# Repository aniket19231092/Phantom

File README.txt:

Phantom ESP32
A lightweight open-source bicycle navigation computer built with the ESP32.

Phantom is a DIY GPS cycling computer designed for outdoor use. It combines an ESP32, u-blox MAX-M10M GPS receiver, Sharp Memory LCD, and microSD card to create a low-power navigation device capable of displaying maps, tracking rides, and providing real-time cycling metrics. Checkout the Pictures folder for pictures of the PCB and enclosure.

The Sharp Memory LCD provides excellent sunlight readability while consuming very little power, making it ideal for long rides.

This is a good project for those getting into embedded electronics and SMD soldering.
---
CAD
Only two parts are needed to be 3D printed, the top and bottom enclosure, which are found in the CAD folder. ABS is preferred because it needs to be able to
withstand the Sun. For assembly 4 M3 screws are needed, about 4-6mm in length is needed.

---
Features

- 🗺️ Offline map rendering from microSD card
- 📍 Real-time GPS positioning using the u-blox MAX-M10M
- 🚴 Live cycling data
  - Current speed
  - Average speed
  - Trip distance
  - Total distance
  - Heading
  - Ride time
- 🧭 Turn-by-turn capable map interface (planned)
- 💾 GPX ride logging to SD card
- 🌞 Sunlight-readable Sharp Memory LCD
- 🔋 Low power design for extended battery life
- 📡 Fast satellite acquisition with multi-band GNSS support
- Bluetooth capabilities for uploading to fitness apps such as Strava

---
Hardware

| Component | Description |
|------------|-------------|
| ESP32 | Main processor |
| MAX-M10M GPS | High-performance GNSS receiver |
| Sharp Memory LCD | Outdoor-readable display |
| microSD Card Module | Offline maps and GPX storage |
| Li-Ion/LiPo Battery | Portable power |
| Battery Charger | USB charging circuit|
| Handlebar Mount | Bicycle mounting system |

Offline Maps

Maps are stored on the microSD card and loaded as needed.

Possible formats include:

- Raster map tiles
- Vector tiles (future)
- Custom compressed tile database

The map renderer centers on the current GPS position while displaying nearby roads and paths.

---

Ride Data

The computer continuously records:

- Current speed
- Average speed
- Maximum speed
- Total distance
- Ride duration
- GPS track
- Timestamp
- Latitude
- Longitude

Tracks are stored as GPX files for later upload to services such as Strava or Garmin Connect.

---

Why Sharp Memory LCD?

Unlike TFT or OLED displays, the Sharp Memory LCD offers:

- Excellent readability in direct sunlight
- Extremely low power consumption
- No backlight required during daytime
- Fast refresh for navigation
- Long battery life

These characteristics make it particularly well-suited for bicycle computers and outdoor GPS devices.

---

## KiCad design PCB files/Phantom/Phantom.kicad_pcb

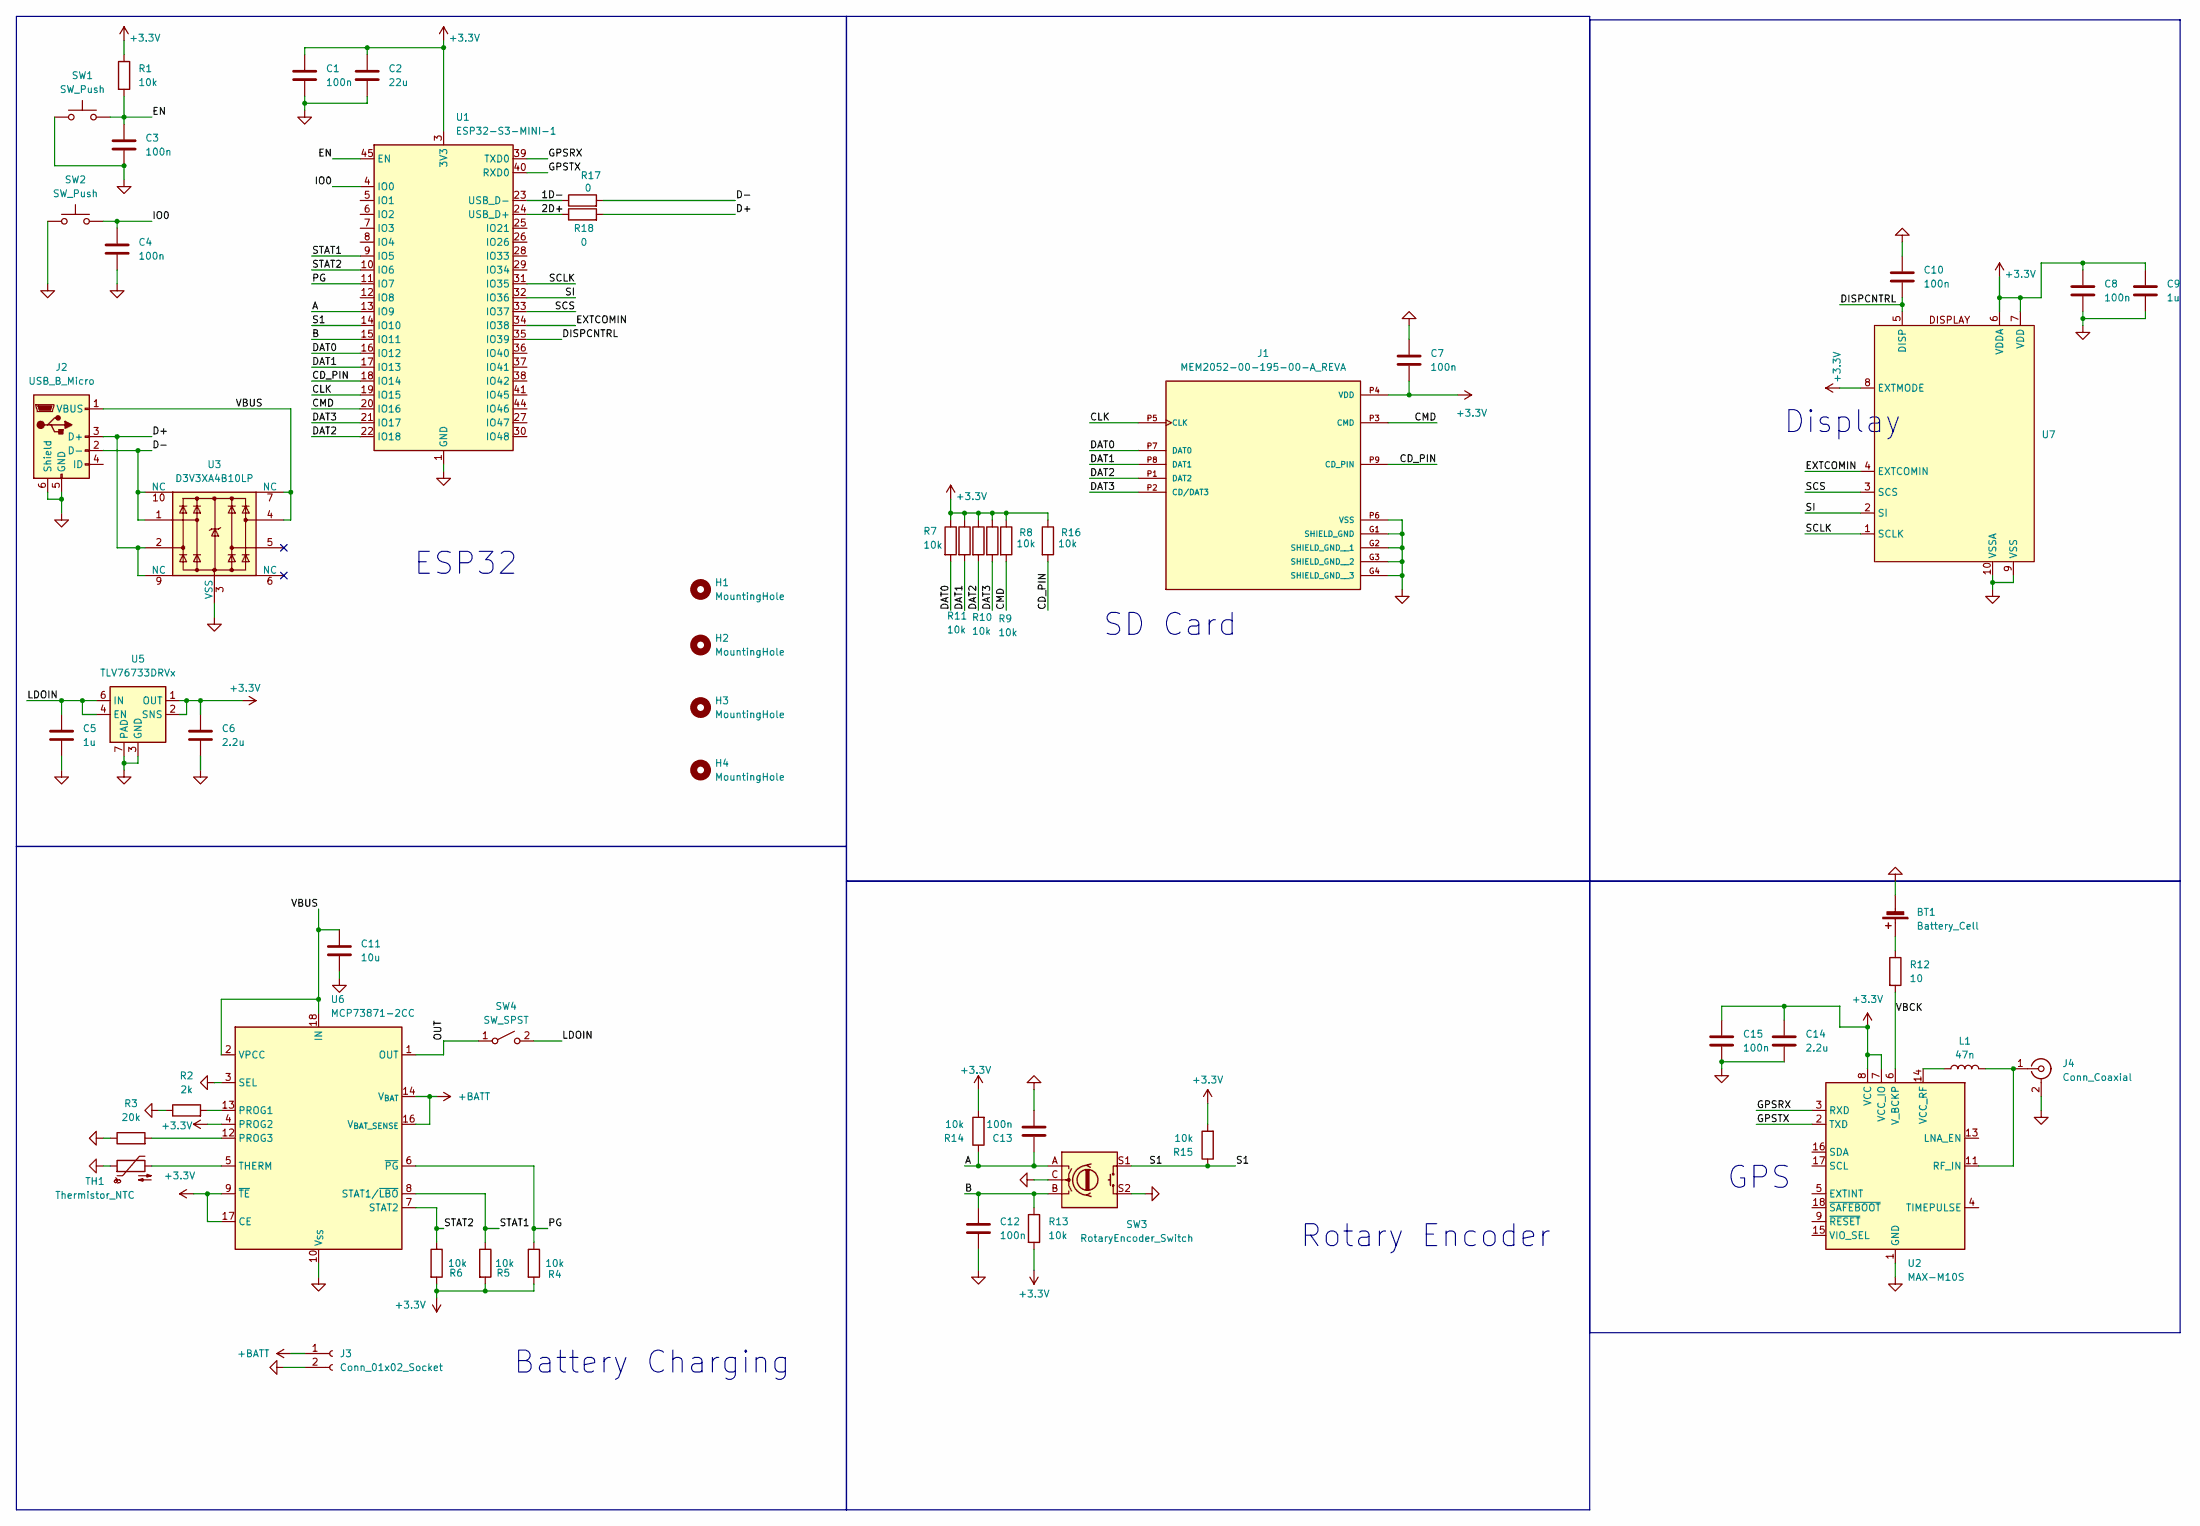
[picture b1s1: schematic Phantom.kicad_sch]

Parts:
BT1: Battery_Cell; BAT_BC501SM
C1, C3, C4, C7, C8, C10, C12, C13, C15: 100n; C_0603_1608Metric
C2: 22u; C_0805_2012Metric
C5, C9: 1u; C_0603_1608Metric
C6, C14: 2.2u; C_0603_1608Metric
C11: 10u; C_0805_2012Metric
H1, H2, H3, H4: MountingHole; MountingHole_3.2mm_M3
J1: MEM2052-00-195-00-A_REVA; GCT_MEM2052-00-195-00-A_REVA; PARTREV A
J2: USB_B_Micro; JAE_DX4R005HJ5R2000
J3: Conn_01x02_Socket; JST_PH_S2B-PH-K_1x02_P2.00mm_Horizontal
J4: Conn_Coaxial; U.FL_Hirose_U.FL-R-SMT-1_Vertical
L1: 47n; L_0603_1608Metric
R1, R4, R5, R6, R7, R8, R9, R10, R11, R13, R14, R15, R16: 10k; R_0603_1608Metric
R2: 2k; R_0603_1608Metric
R3: 20k; R_0603_1608Metric
R12: 10; R_0603_1608Metric
R17, R18: 0; R_0603_1608Metric
SW1, SW2: SW_Push; SW_B3U-1100P
SW3: RotaryEncoder_Switch; COM-15141_SPK
SW4: SW_SPST; SW_1MS02Q_CNK
TH1: Thermistor_NTC; R_0603_1608Metric
U1: ESP32-S3-MINI-1; ESP32-S3-MINI-1_EXP
U2: MAX-M10S; ublox_MAX
U3: D3V3XA4B10LP; Diodes_UDFN-10_1.0x2.5mm_P0.5mm
U5: TLV76733DRVx; WSON-6-1EP_2x2mm_P0.65mm_EP1x1.6mm_ThermalVias
U6: MCP73871-2CC; QFN-20-1EP_4x4mm_P0.5mm_EP2.5x2.5mm
U7: HRS_FH33-10S-0.5SH_10_

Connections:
+3.3V: C1.1, C2.1, C6.1, C7.1, C8.1, C9.1, C14.2, C15.2, J1.P4 (VDD), R1.1, R4.2, R5.2, R6.2, R7.1, R8.1, R9.1, R10.1, R11.1, R13.2, R14.2, R15.2, R16.1, U1.3 (3V3), U2.7 (VCC_IO), U2.8 (VCC), U5.1 (OUT), U5.2 (SNS), U6.4 (PROG2), U6.9 (~TE), U6.17 (CE), U7.6 (VDDA), U7.7 (VDD), U7.8 (EXTMODE)
+BATT: J3.1, U6.14 (V_{BAT}), U6.15 (V_{BAT}), U6.16 (V_{BAT_SENSE})
/1D-: R17.1, U1.23 (USB_D-)
/2D+: R18.1, U1.24 (USB_D+)
/A: C13.1, R14.1, SW3.A, U1.13 (IO9)
/B: C12.1, R13.1, SW3.B, U1.15 (IO11)
/CD_PIN: J1.P9 (CD_PIN), R16.2, U1.18 (IO14)
/CLK: J1.P5 (CLK), U1.19 (IO15)
/CMD: J1.P3 (CMD), R8.2, U1.20 (IO16)
/D+: J2.3 (D+), R18.2, U3.2, U3.9 (NC)
/D-: J2.2 (D-), R17.2, U3.1, U3.10 (NC)
/DAT0: J1.P7 (DAT0), R7.2, U1.16 (IO12)
/DAT1: J1.P8 (DAT1), R11.2, U1.17 (IO13)
/DAT2: J1.P1 (DAT2), R10.2, U1.22 (IO18)
/DAT3: J1.P2 (CD/DAT3), R9.2, U1.21 (IO17)
/DISPCNTRL: C10.1, U1.35 (IO39), U7.5 (DISP)
/EN: C3.1, R1.2, SW1.2, U1.45 (EN)
/EXTCOMIN: U1.34 (IO38), U7.4 (EXTCOMIN)
/GPSRX: U1.39 (TXD0), U2.3 (RXD)
/GPSTX: U1.40 (RXD0), U2.2 (TXD)
/IO0: C4.1, SW2.2, U1.4 (IO0)
/LDOIN: C5.1, SW4.2 (B), U5.4 (EN), U5.6 (IN)
/OUT: SW4.1 (A), U6.1 (OUT), U6.20 (OUT)
/PG: R4.1, U1.11 (IO7), U6.6 (~PG)
/S1: R15.1, SW3.S1, U1.14 (IO10)
/SCLK: U1.31 (IO35), U7.1 (SCLK)
/SCS: U1.33 (IO37), U7.3 (SCS)
/SI: U1.32 (IO36), U7.2 (SI)
/STAT1: R5.1, U1.9 (IO5), U6.8 (STAT1/~LBO)
/STAT2: R6.1, U1.10 (IO6), U6.7 (STAT2)
/VBCK: R12.2, U2.6 (V_BCKP)
/VBUS: C11.1, J2.1 (VBUS), U3.4, U3.7 (NC), U6.2 (VPCC), U6.18 (IN), U6.19 (IN)
GND: BT1.2 (-), C1.2, C2.2, C3.2, C4.2, C5.2, C6.2, C7.2, C8.2, C9.2, C10.2, C11.2, C12.2, C13.2, C14.1, C15.1, J1.G1 (SHIELD_GND), J1.G2 (SHIELD_GND__1), J1.G3 (SHIELD_GND__2), J1.G4 (SHIELD_GND__3), J1.P6 (VSS), J2.5 (GND), J2.6 (Shield), J3.2, J4.2 (Ext), R2.1, R3.1, SW1.1, SW2.1, SW3.C, SW3.S2, TH1.1, U1.1 (GND), U1.2 (GND), U1.42 (GND), U1.43 (GND), U1.46 (GND), U1.47 (GND), U1.48 (GND), U1.49 (GND), U1.50 (GND), U1.51 (GND), U1.52 (GND), U1.53 (GND), U1.54 (GND), U1.55 (GND), U1.56 (GND), U1.57 (GND), U1.58 (GND), U1.59 (GND), U1.60 (GND), U1.61 (GND), U1.62 (GND), U1.63 (GND), U1.64 (GND), U1.65 (GND), U2.1 (GND), U2.10 (GND), U2.12 (GND), U3.3 (VSS), U3.8 (VSS), U5.3 (GND), U5.5 (GND), U5.7 (PAD), U6.3 (SEL), U6.10 (V_{SS}), U6.11 (V_{SS}), U6.21 (V_{SS}), U7.9 (VSS), U7.10 (VSSA)
unnamed: BT1.1 (+), R12.1
unnamed: J4.1 (In), L1.2, U2.11 (RF_IN)
unnamed: L1.1, U2.14 (VCC_RF)
unnamed: R2.2, U6.13 (PROG1)
unnamed: R3.2, U6.12 (PROG3)
unnamed: TH1.2, U6.5 (THERM)

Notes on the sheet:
Battery Charging
Rotary Encoder
ESP32
GPS
Display
SD Card

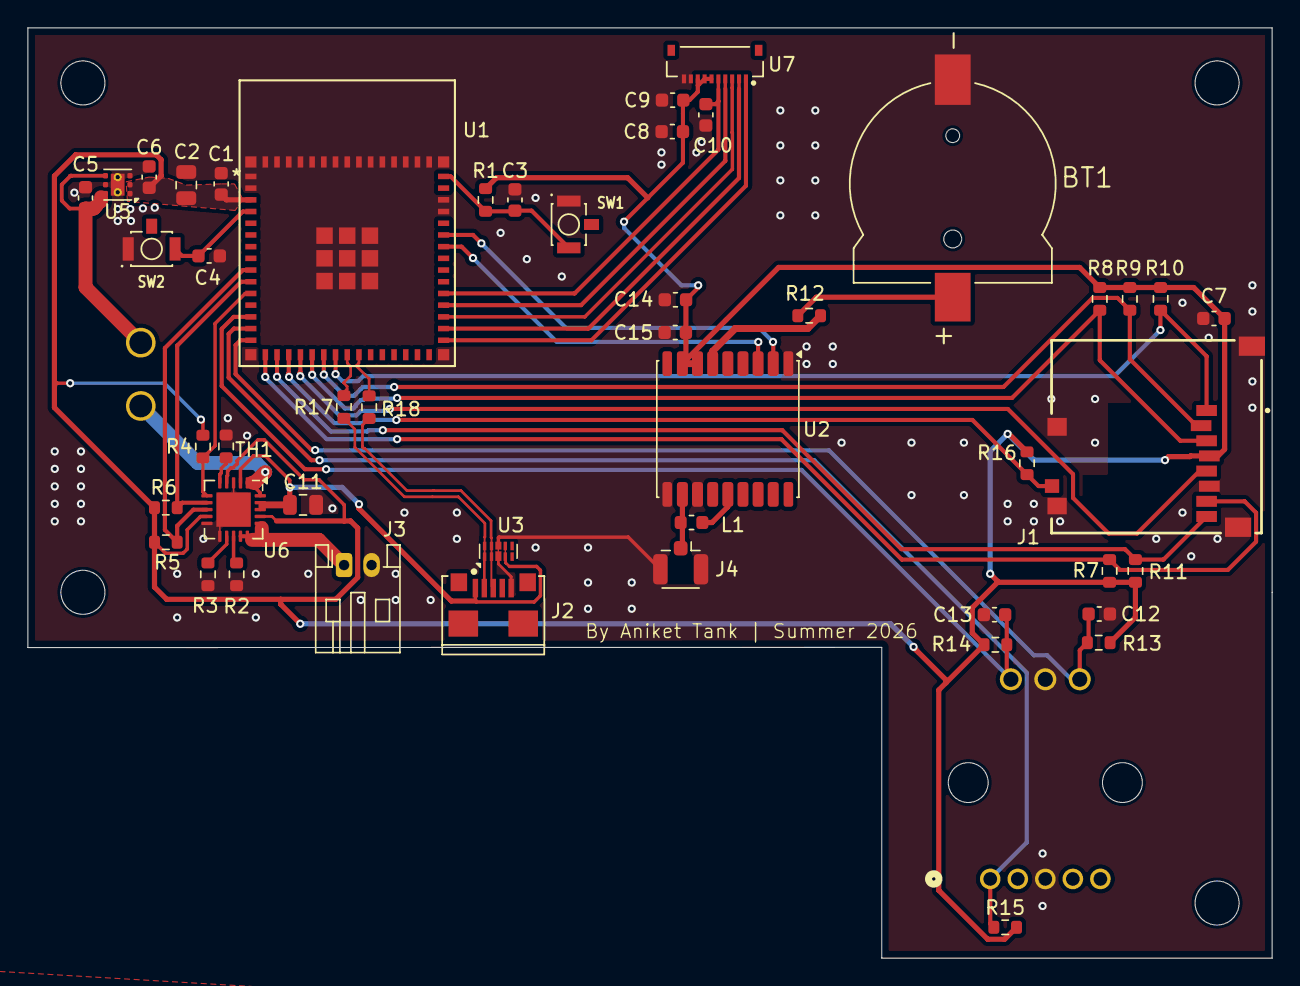
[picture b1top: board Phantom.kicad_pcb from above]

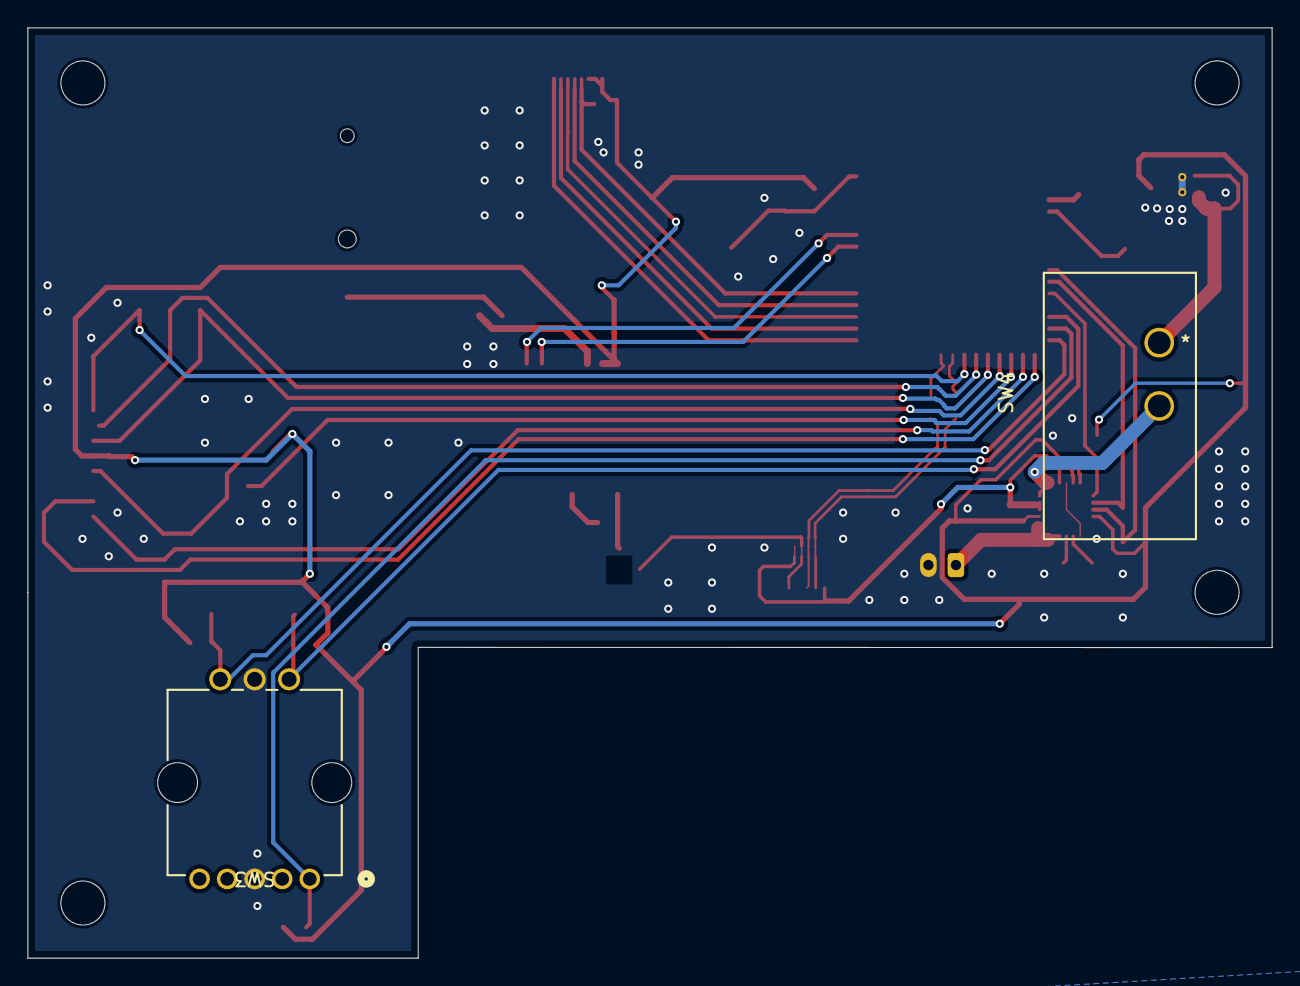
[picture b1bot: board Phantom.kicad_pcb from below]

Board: 2 copper layers, 90.4 x 67.6 mm, 54 parts (2 on the bottom side), 39 nets.

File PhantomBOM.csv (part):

Item Name,Qty,Price (total) (USD),Item link,Notes,PCB Designator
ESP32-S3-MINI1,1,$5.43,https://www.digikey.com/en/products/detail/espressif-systems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,ESP32 Microcontroller and bluetooth,U1
MEM2052-00-195-00-A,1,$1.14,https://www.digikey.com/en/products/detail/gct/MEM2052-00-19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,SD Card,J1
MAX-M10M-00B,1,$7.56,https://www.digikey.com/en/products/detail/u-blox/MAX-M10M-0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,GPS Chip,U2
DX4R005HJ5R2000,1,$0.80,https://www.digikey.com/en/products/detail/jae-electronics/D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,USB,J2
LS027B7DH01A,1,$27.59,https://www.digikey.com/en/products/detail/sharp-microelectr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,Display,U7
B57330V2103J260,1,$0.19,https://www.digikey.com/en/products/detail/tdk/B57330V2103J2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,Thermistor,TH1
D3V3XA4B10LP-7,1,$0.44,https://www.digikey.com/en/products/detail/diodes-incorporat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,EMI Protection,U3
TLV76733DRVR,1,$1.05,https://www.digikey.com/en/products/detail/texas-instruments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,Linear Voltage Regulator,U5
MCP73871-2CCI/ML,1,$2.41,https://www.digikey.com/en/products/detail/microchip-technol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,Battery Charging,U6
B3U-1100P,2,$1.17,https://www.digikey.com/en/products/detail/omron-electronics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,Push Button,"SW1,SW2"
PCB,1,$121.62,,Qoute from JLC PCB includes shipping/tarrifs,
BC501SM,1,$1.37,https://www.digikey.com/en/products/detail/mpd-memory-protec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,Coin battery holder,BT1
15141,1,$4.96,https://www.digikey.com/en/products/detail/sparkfun-electron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,Rotary Encoder,SW3
L101011MS02Q,1,$3.97,https://www.digikey.com/en/products/detail/c-k/L101011MS02Q/484142,Power Switch,SW4
FH33-10S-0.5SH(10),1,$1.22,https://www.digikey.com/en/products/detail/hirose-electric-c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,Screen Connector,U7
AGGP.25F.07.0060A,1,$19.30,https://www.digikey.com/en/products/detail/taoglas-limited/a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,GPS Antenna,
U.FL-R-SMT-K(895),1,$1.29,https://www.digikey.com/en/products/detail/hirose-electric-c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,GPS Antenna Connector,J4
B2B-PH-SM4-TB,1,$0.47,https://www.digikey.com/en/models/926641?tab=snapmagic,Battery Connector,J3
C0603C104K5RACTU,9,$0.10,https://www.digikey.com/en/products/detail/kemet/C0603C104K5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,100nF Capacitor,"C1,C3,C4,C7,C8,C10,C12,C13,C15"
C1608X5R1H105K080AB,2,$0.16,https://www.digikey.com/en/products/detail/tdk/C1608X5R1H105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,1uF Capacitor,"C5,C9"
CL21A226KOQNNNE,1,$0.35,https://www.digikey.com/en/products/detail/samsung-electro-m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,22uF Capacitor,C2
CL21A225KOFNNNE,2,$0.13,https://www.digikey.com/en/products/detail/samsung-electro-m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,2.2uF Capacitor,"C6,C14"
CL21A106KOFNNNE,1,$0.16,https://www.digikey.com/en/products/detail/samsung-electro-m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,10uF Capcitor,C11
CR0603-FX-1002ELF,13,$0.10,https://www.digikey.com/en/products/detail/bourns-inc/CR0603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,10k Ohm Resistor,"R1,R4,R5,R6,R7,R8,R9,R10,11,R13,R14,R15,R16"
CR2512-FX-2001ELF,1,$0.23,https://www.digikey.com/en/products/detail/bourns-inc/CR2512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,2k Ohm Resistor,R2
RN73H1JTTD2032D25,1,$0.10,https://www.digikey.com/en/products/detail/koa-speer-electro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,20k Ohm Resistor,R3
CRGH0603F10R,1,$0.12,https://www.digikey.com/en/products/detail/te-connectivity-p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,10 Ohm Resistor,R12
MCT06030Z0000ZP500,2,$0.19,https://www.digikey.com/en/products/detail/vishay/MCT06030Z0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,0 Ohm Resistor,"R17,R18"
Total Price (USD):,207.27,,,,
,,,,,
,,,,,
,,,,,
,,,,,
,,,,,
,,,,,
,,,,,
,,,,,
,,,,,
,,,,,
,,,,,
,,,,,
,,,,,
,,,,,
,,,,,
,,,,,
,,,,,
,,,,,
,,,,,
,,,,,
,,,,,
,,,,,
,,,,,
,,,,,
,,,,,
,,,,,
,,,,,
,,,,,
,,,,,
,,,,,
,,,,,
,,,,,
,,,,,
,,,,,
,,,,,
,,,,,
,,,,,
,,,,,
,,,,,
,,,,,
,,,,,
,,,,,
,,,,,
,,,,,
,,,,,
,,,,,
,,,,,
,,,,,
,,,,,
,,,,,
,,,,,
,,,,,
,,,,,
,,,,,
,,,,,
,,,,,
,,,,,
,,,,,
,,,,,
,,,,,
,,,,,
,,,,,
,,,,,
,,,,,
,,,,,
,,,,,
,,,,,
,,,,,
,,,,,
,,,,,
,,,,,
,,,,,
,,,,,
,,,,,
,,,,,
,,,,,
,,,,,
,,,,,
,,,,,
,,,,,
,,,,,
,,,,,
,,,,,
,,,,,
,,,,,
,,,,,
,,,,,
,,,,,
,,,,,
,,,,,
,,,,,
,,,,,
,,,,,
,,,,,
,,,,,
,,,,,
,,,,,
,,,,,
,,,,,
,,,,,
,,,,,
,,,,,
,,,,,
,,,,,
,,,,,
,,,,,
,,,,,
,,,,,
,,,,,
,,,,,
,,,,,
,,,,,
,,,,,
,,,,,
,,,,,
,,,,,
,,,,,
,,,,,
,,,,,
,,,,,
,,,,,
,,,,,
,,,,,
,,,,,
,,,,,
,,,,,
,,,,,
,,,,,
,,,,,
,,,,,
,,,,,
,,,,,
,,,,,
,,,,,
,,,,,
,,,,,
,,,,,
,,,,,
,,,,,
,,,,,
,,,,,
,,,,,
,,,,,
,,,,,
,,,,,
,,,,,
,,,,,
,,,,,
,,,,,
,,,,,
,,,,,
,,,,,
,,,,,
,,,,,
,,,,,
,,,,,
,,,,,
,,,,,
,,,,,
,,,,,
,,,,,
,,,,,
,,,,,
,,,,,
,,,,,
,,,,,
,,,,,
,,,,,
,,,,,
,,,,,
,,,,,
,,,,,
,,,,,
,,,,,
,,,,,
,,,,,
,,,,,
,,,,,
,,,,,
,,,,,
,,,,,
,,,,,
,,,,,
,,,,,
,,,,,
,,,,,
,,,,,
,,,,,
,,,,,
,,,,,
,,,,,
,,,,,
,,,,,
,,,,,
,,,,,
,,,,,
,,,,,
,,,,,
,,,,,
,,,,,
,,,,,
,,,,,
,,,,,
,,,,,
,,,,,
,,,,,
,,,,,
,,,,,
,,,,,
,,,,,
,,,,,
,,,,,
,,,,,
,,,,,
,,,,,
,,,,,
,,,,,
,,,,,
,,,,,
,,,,,
,,,,,
,,,,,
,,,,,
,,,,,
,,,,,
,,,,,
,,,,,
,,,,,
,,,,,
,,,,,
,,,,,
,,,,,
,,,,,
,,,,,
,,,,,
,,,,,
,,,,,
,,,,,
,,,,,
,,,,,
,,,,,
,,,,,
,,,,,
,,,,,
,,,,,
,,,,,
,,,,,
,,,,,
,,,,,
,,,,,
,,,,,
,,,,,
,,,,,
,,,,,
,,,,,
,,,,,
,,,,,
,,,,,
,,,,,
,,,,,
,,,,,
,,,,,
,,,,,
,,,,,
,,,,,
,,,,,
,,,,,
,,,,,
,,,,,
,,,,,
,,,,,
,,,,,
,,,,,
,,,,,
,,,,,
,,,,,
,,,,,
,,,,,
,,,,,
,,,,,
,,,,,
,,,,,
,,,,,
,,,,,
,,,,,
,,,,,
,,,,,
,,,,,
,,,,,
,,,,,
,,,,,
,,,,,
,,,,,
,,,,,
,,,,,
,,,,,
,,,,,
,,,,,
,,,,,
,,,,,
,,,,,
,,,,,
,,,,,
,,,,,
,,,,,
,,,,,
,,,,,
,,,,,
,,,,,
,,,,,
,,,,,
,,,,,
,,,,,
,,,,,
,,,,,
,,,,,
,,,,,
,,,,,
,,,,,
,,,,,
,,,,,
,,,,,
,,,,,
,,,,,
,,,,,
,,,,,
,,,,,
,,,,,
,,,,,
,,,,,
,,,,,
,,,,,
,,,,,
,,,,,
,,,,,
,,,,,
,,,,,
,,,,,
,,,,,
,,,,,
,,,,,
,,,,,
,,,,,
,,,,,
,,,,,
,,,,,
,,,,,
,,,,,
,,,,,
,,,,,
,,,,,
,,,,,
,,,,,
,,,,,
,,,,,
,,,,,
,,,,,
,,,,,
,,,,,
,,,,,
,,,,,
,,,,,
,,,,,
,,,,,
,,,,,
,,,,,
,,,,,
,,,,,
,,,,,
,,,,,
,,,,,
,,,,,
,,,,,
,,,,,
,,,,,
,,,,,
,,,,,
,,,,,
,,,,,
,,,,,
,,,,,
,,,,,
,,,,,
,,,,,
,,,,,
,,,,,
,,,,,
,,,,,
,,,,,
,,,,,
,,,,,
,,,,,
,,,,,
,,,,,
,,,,,
,,,,,
,,,,,
,,,,,
,,,,,
,,,,,
,,,,,
,,,,,
,,,,,
,,,,,
,,,,,
,,,,,
,,,,,
,,,,,
,,,,,
,,,,,
,,,,,
,,,,,
,,,,,
,,,,,
,,,,,
,,,,,
,,,,,
,,,,,
,,,,,
,,,,,
,,,,,
,,,,,
,,,,,
,,,,,
,,,,,
,,,,,
,,,,,
,,,,,
,,,,,
,,,,,
,,,,,
,,,,,
,,,,,
,,,,,
,,,,,
,,,,,
,,,,,
,,,,,
,,,,,
,,,,,
,,,,,
,,,,,
,,,,,
,,,,,
,,,,,
,,,,,
,,,,,
,,,,,
,,,,,
,,,,,
,,,,,
,,,,,
,,,,,
,,,,,
,,,,,
,,,,,
,,,,,
,,,,,
,,,,,
,,,,,
,,,,,
,,,,,
,,,,,
,,,,,
,,,,,
,,,,,
,,,,,
,,,,,
,,,,,
,,,,,
,,,,,
,,,,,
,,,,,
,,,,,
,,,,,
,,,,,
,,,,,
,,,,,
,,,,,
,,,,,
,,,,,
,,,,,
,,,,,
,,,,,
,,,,,
,,,,,
,,,,,
,,,,,
,,,,,
,,,,,
,,,,,
,,,,,
,,,,,
,,,,,
,,,,,
,,,,,
,,,,,
,,,,,
,,,,,
,,,,,
,,,,,
,,,,,
,,,,,
,,,,,
,,,,,
,,,,,
,,,,,
,,,,,
,,,,,
,,,,,
,,,,,
,,,,,
,,,,,
,,,,,
,,,,,
,,,,,
,,,,,
,,,,,
,,,,,
,,,,,
,,,,,
,,,,,
,,,,,
,,,,,
,,,,,
,,,,,
,,,,,
,,,,,
,,,,,
,,,,,
,,,,,
,,,,,
,,,,,
,,,,,
,,,,,
,,,,,
,,,,,
,,,,,
,,,,,
,,,,,
,,,,,
,,,,,
,,,,,
,,,,,
,,,,,
,,,,,
,,,,,
,,,,,
,,,,,
,,,,,
,,,,,
,,,,,
,,,,,
,,,,,
,,,,,
,,,,,
,,,,,
,,,,,
,,,,,
,,,,,
,,,,,
,,,,,
,,,,,
,,,,,
,,,,,
,,,,,
,,,,,
,,,,,
,,,,,
,,,,,
,,,,,
,,,,,
,,,,,
,,,,,
,,,,,
,,,,,
,,,,,
,,,,,
,,,,,
,,,,,
,,,,,
,,,,,
,,,,,
,,,,,
,,,,,
,,,,,
,,,,,
,,,,,
,,,,,
,,,,,
,,,,,
,,,,,
,,,,,
,,,,,
,,,,,
,,,,,
,,,,,
,,,,,
,,,,,
,,,,,
,,,,,
,,,,,
,,,,,
,,,,,
,,,,,
,,,,,
,,,,,
,,,,,
,,,,,
,,,,,
,,,,,
,,,,,
,,,,,
,,,,,
,,,,,
,,,,,
,,,,,
,,,,,
,,,,,
,,,,,
,,,,,
,,,,,
,,,,,
,,,,,
,,,,,
,,,,,
,,,,,
,,,,,
,,,,,
,,,,,
,,,,,
,,,,,
,,,,,
,,,,,
,,,,,
,,,,,
,,,,,
,,,,,
,,,,,
,,,,,
,,,,,
,,,,,
,,,,,
,,,,,
,,,,,
,,,,,
,,,,,
,,,,,
,,,,,
,,,,,
,,,,,
,,,,,
,,,,,
,,,,,
,,,,,
,,,,,
,,,,,
,,,,,
,,,,,
,,,,,
,,,,,
,,,,,
,,,,,
,,,,,
,,,,,
,,,,,
,,,,,
,,,,,
,,,,,
,,,,,
,,,,,
,,,,,
,,,,,
,,,,,
,,,,,
,,,,,
,,,,,
,,,,,
,,,,,
,,,,,
,,,,,
,,,,,
,,,,,
,,,,,
,,,,,
,,,,,
,,,,,
,,,,,
,,,,,
,,,,,
,,,,,
,,,,,
,,,,,
,,,,,
,,,,,
,,,,,
,,,,,
,,,,,
,,,,,
,,,,,
,,,,,
,,,,,
,,,,,
,,,,,
,,,,,
,,,,,
,,,,,
,,,,,
,,,,,
,,,,,
,,,,,
,,,,,
,,,,,
,,,,,
,,,,,
,,,,,
,,,,,
,,,,,
,,,,,
,,,,,
,,,,,
,,,,,
,,,,,
,,,,,
,,,,,
,,,,,
,,,,,
,,,,,
,,,,,
,,,,,
,,,,,
,,,,,
,,,,,
,,,,,
,,,,,
,,,,,
,,,,,
,,,,,
,,,,,
,,,,,
,,,,,
,,,,,
,,,,,
,,,,,
,,,,,
,,,,,
,,,,,
,,,,,
,,,,,
,,,,,
,,,,,
,,,,,
,,,,,
,,,,,
,,,,,
,,,,,
,,,,,
,,,,,
,,,,,
,,,,,
,,,,,
,,,,,
,,,,,
,,,,,
,,,,,
,,,,,
,,,,,
,,,,,
,,,,,
,,,,,
,,,,,
,,,,,
,,,,,
,,,,,
,,,,,
,,,,,
,,,,,
,,,,,
,,,,,
,,,,,
,,,,,
,,,,,
,,,,,
,,,,,
,,,,,
,,,,,
,,,,,
,,,,,
,,,,,
,,,,,
,,,,,
,,,,,
,,,,,
,,,,,
,,,,,
,,,,,
,,,,,
,,,,,
,,,,,
,,,,,
,,,,,
,,,,,
,,,,,
,,,,,
,,,,,
,,,,,
,,,,,
,,,,,
,,,,,
,,,,,
,,,,,
,,,,,
,,,,,
,,,,,
,,,,,
,,,,,
,,,,,
,,,,,
,,,,,
,,,,,
,,,,,
,,,,,
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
